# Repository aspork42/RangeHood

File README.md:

# RangeHood
# RangeHood
# RangeHood

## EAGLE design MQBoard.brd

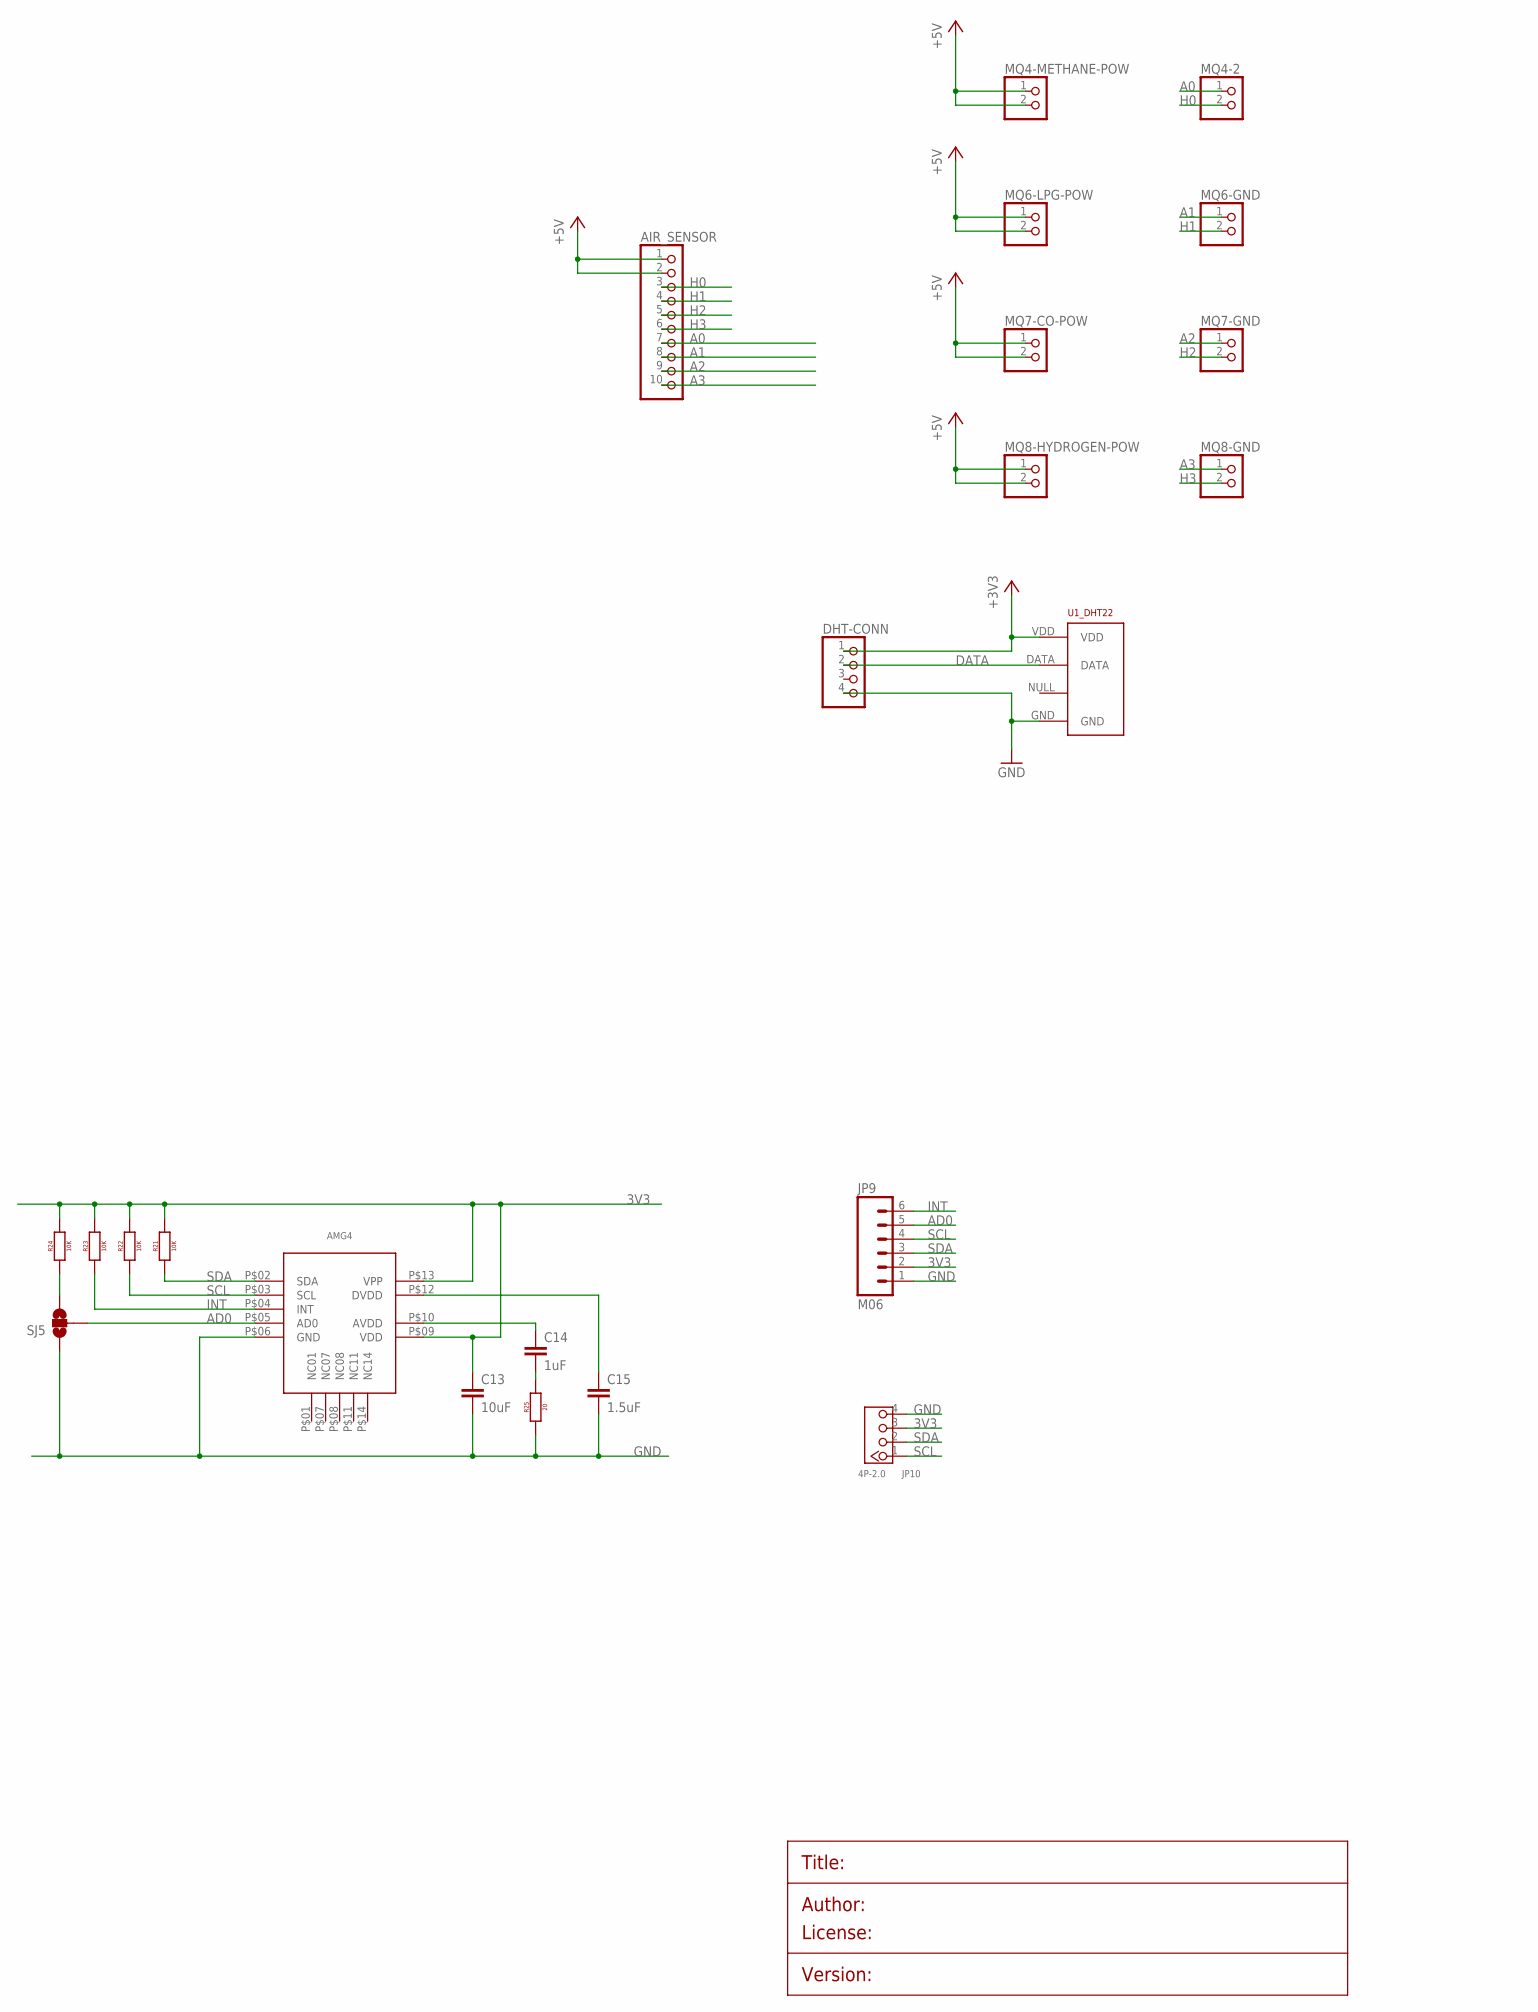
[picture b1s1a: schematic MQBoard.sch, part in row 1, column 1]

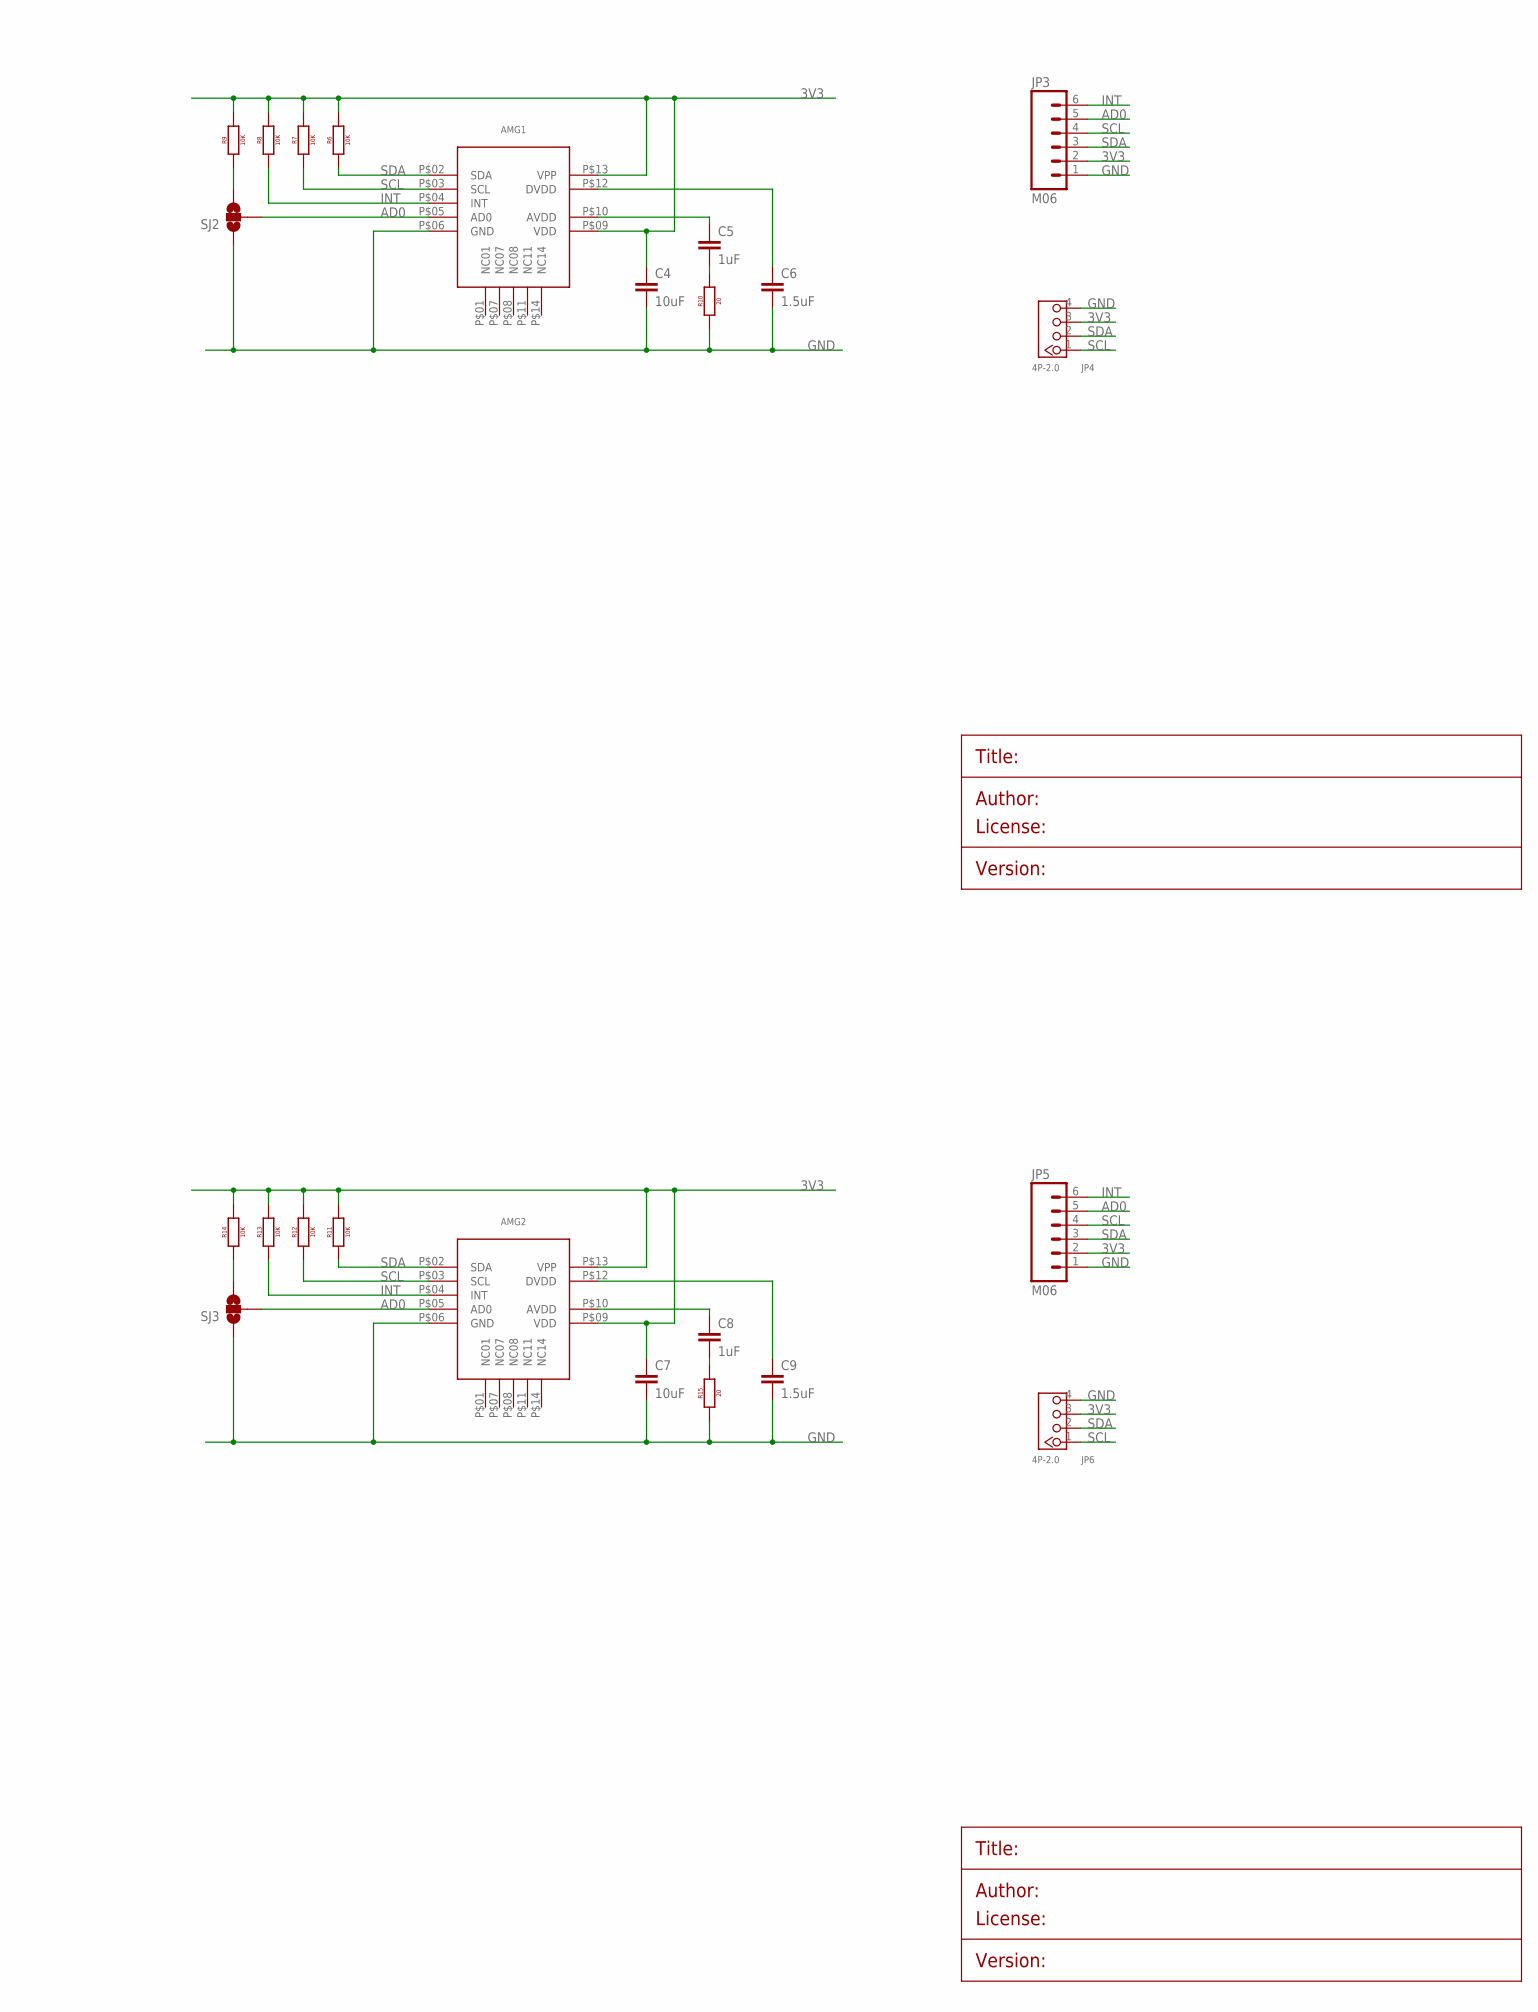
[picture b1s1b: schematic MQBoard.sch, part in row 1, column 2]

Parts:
AIR_SENSOR: PINHD-1X10; 1X10
AMG1, AMG2, AMG4: AMG88XX
C4, C7, C13: 10uF; 0805
C5, C8, C14: 1uF; 0805
C6, C9, C15: 1.5uF; 0805
DHT-CONN: PINHD-1X4; 1X04
JP3, JP5, JP9: M06; 1X06_NO_SILK
JP4, JP6, JP10: 4P-2.0; HW4-2.0
MQ4-2, MQ4-METHANE-POW, MQ6-GND, MQ6-LPG-POW, MQ7-CO-POW, MQ7-GND, MQ8-GND, MQ8-HYDROGEN-POW: PINHD-1X2; 1X02
R6, R7, R8, R9, R11, R12, R13, R14, R21, R22, R23, R24: 10K; 0805
R10, R15, R25: 20; 0805
SJ2, SJ3, SJ5: SOLDERJUMPER_2WAYS; SJ_3
U1_DHT22: RHT03_DHT-22_AM2302; RHT03_DHT-22

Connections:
3V3: AMG1.P$09 (VDD), AMG1.P$13 (VPP), AMG2.P$09 (VDD), AMG2.P$13 (VPP), AMG4.P$09 (VDD), AMG4.P$13 (VPP), C4.1, C7.1, C13.1, JP3.2, JP4.3, JP5.2, JP6.3, JP9.2, JP10.3, R6.2, R7.2, R8.2, R9.2, R11.2, R12.2, R13.2, R14.2, R21.2, R22.2, R23.2, R24.2
+3V3: DHT-CONN.1, U1_DHT22.VDD
+5V: AIR_SENSOR.1, AIR_SENSOR.2, MQ4-METHANE-POW.1, MQ4-METHANE-POW.2, MQ6-LPG-POW.1, MQ6-LPG-POW.2, MQ7-CO-POW.1, MQ7-CO-POW.2, MQ8-HYDROGEN-POW.1, MQ8-HYDROGEN-POW.2
A0: AIR_SENSOR.7, MQ4-2.1
A1: AIR_SENSOR.8, MQ6-GND.1
A2: AIR_SENSOR.9, MQ7-GND.1
A3: AIR_SENSOR.10, MQ8-GND.1
AD0: AMG1.P$05 (AD0), AMG2.P$05 (AD0), AMG4.P$05 (AD0), JP3.5, JP5.5, JP9.5, SJ2.2, SJ3.2, SJ5.2
DATA: DHT-CONN.2, U1_DHT22.DATA
GND: AMG1.P$06 (GND), AMG2.P$06 (GND), AMG4.P$06 (GND), C4.2, C6.2, C7.2, C9.2, C13.2, C15.2, DHT-CONN.4, JP3.1, JP4.4, JP5.1, JP6.4, JP9.1, JP10.4, R10.1, R15.1, R25.1, SJ2.1, SJ3.1, SJ5.1, U1_DHT22.GND
H0: AIR_SENSOR.3, MQ4-2.2
H1: AIR_SENSOR.4, MQ6-GND.2
H2: AIR_SENSOR.5, MQ7-GND.2
H3: AIR_SENSOR.6, MQ8-GND.2
INT: AMG1.P$04 (INT), AMG2.P$04 (INT), AMG4.P$04 (INT), JP3.6, JP5.6, JP9.6, R8.1, R13.1, R23.1
unnamed: AMG1.P$12 (DVDD), C6.1
unnamed: AMG1.P$10 (AVDD), C5.1
unnamed: R9.1, SJ2.3
unnamed: C5.2, R10.2
unnamed: AMG2.P$12 (DVDD), C9.1
unnamed: AMG2.P$10 (AVDD), C8.1
unnamed: R14.1, SJ3.3
unnamed: C8.2, R15.2
unnamed: AMG4.P$12 (DVDD), C15.1
unnamed: AMG4.P$10 (AVDD), C14.1
unnamed: R24.1, SJ5.3
unnamed: C14.2, R25.2
SCL: AMG1.P$03 (SCL), AMG2.P$03 (SCL), AMG4.P$03 (SCL), JP3.4, JP4.1, JP5.4, JP6.1, JP9.4, JP10.1, R7.1, R12.1, R22.1
SDA: AMG1.P$02 (SDA), AMG2.P$02 (SDA), AMG4.P$02 (SDA), JP3.3, JP4.2, JP5.3, JP6.2, JP9.3, JP10.2, R6.1, R11.1, R21.1

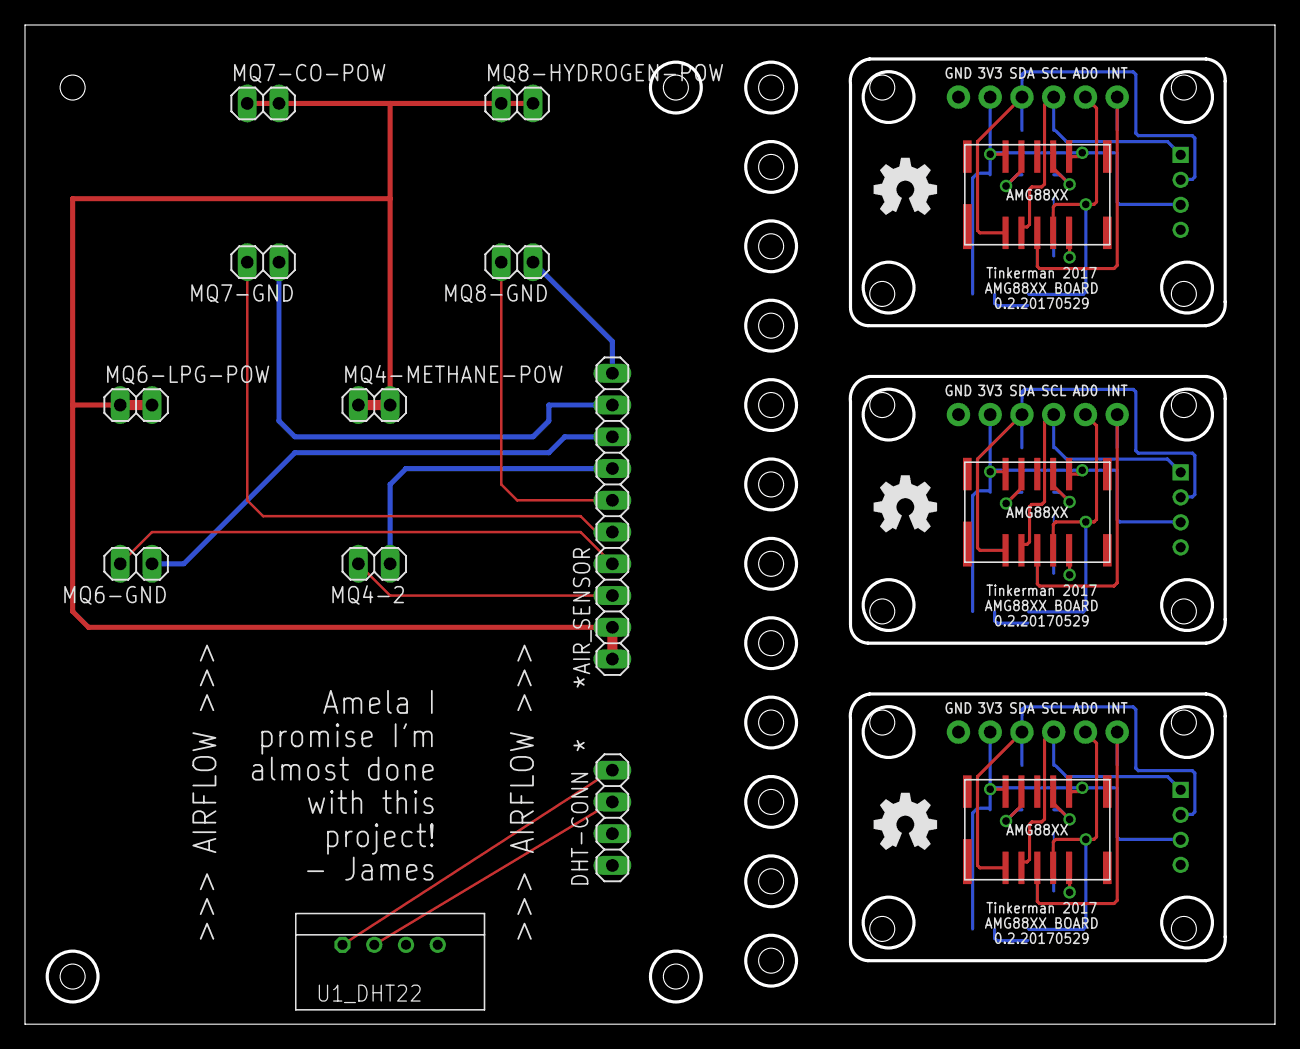
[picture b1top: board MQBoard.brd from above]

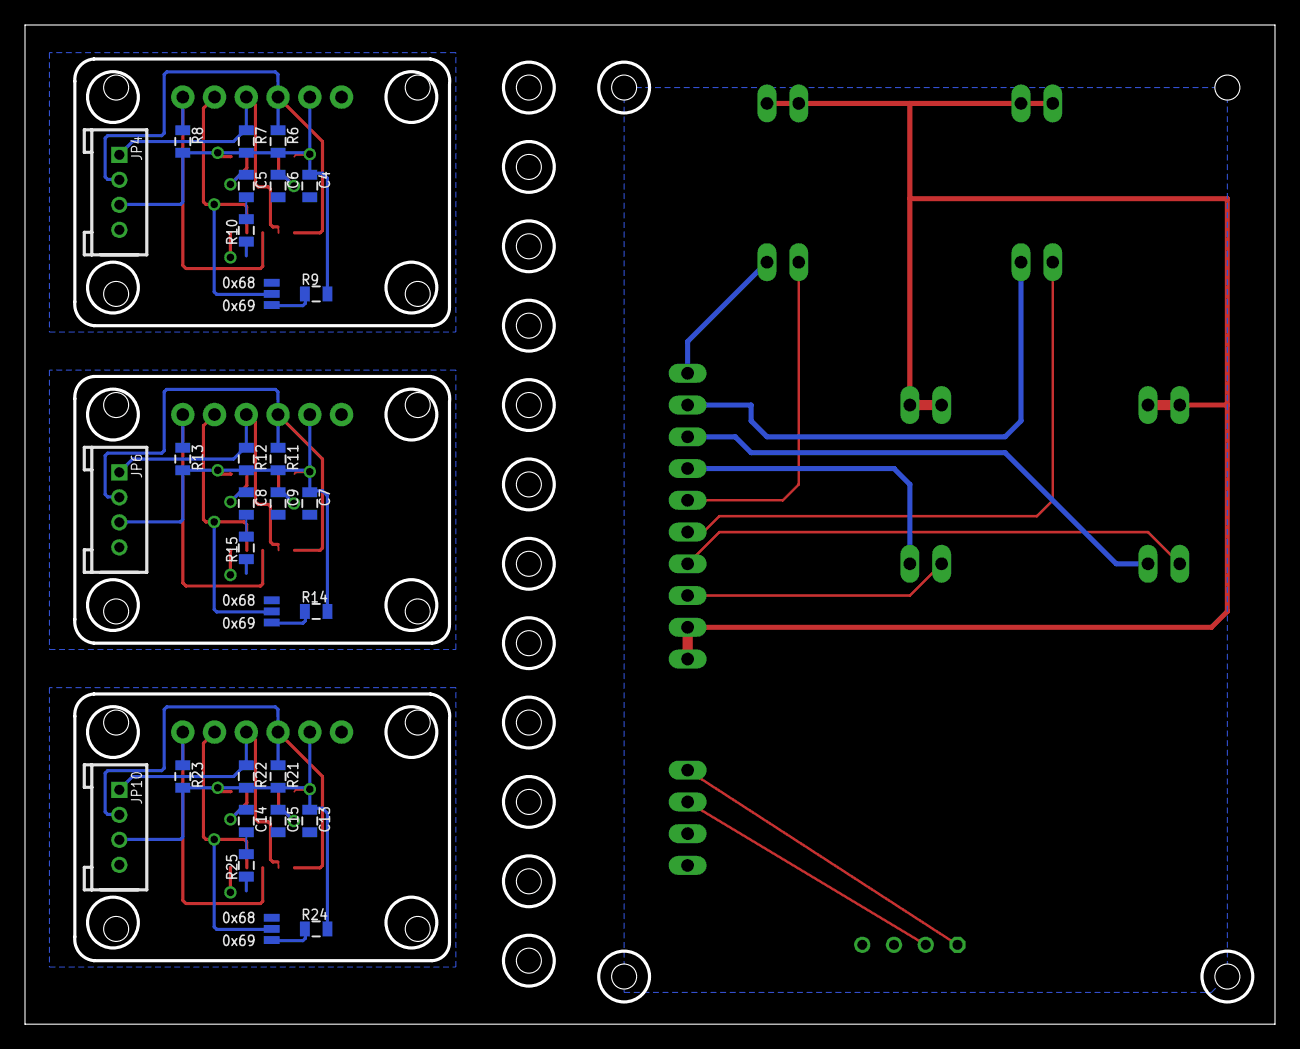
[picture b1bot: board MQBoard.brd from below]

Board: 2 copper layers, 99.7 x 79.7 mm, 47 parts (30 on the bottom side), 29 nets.

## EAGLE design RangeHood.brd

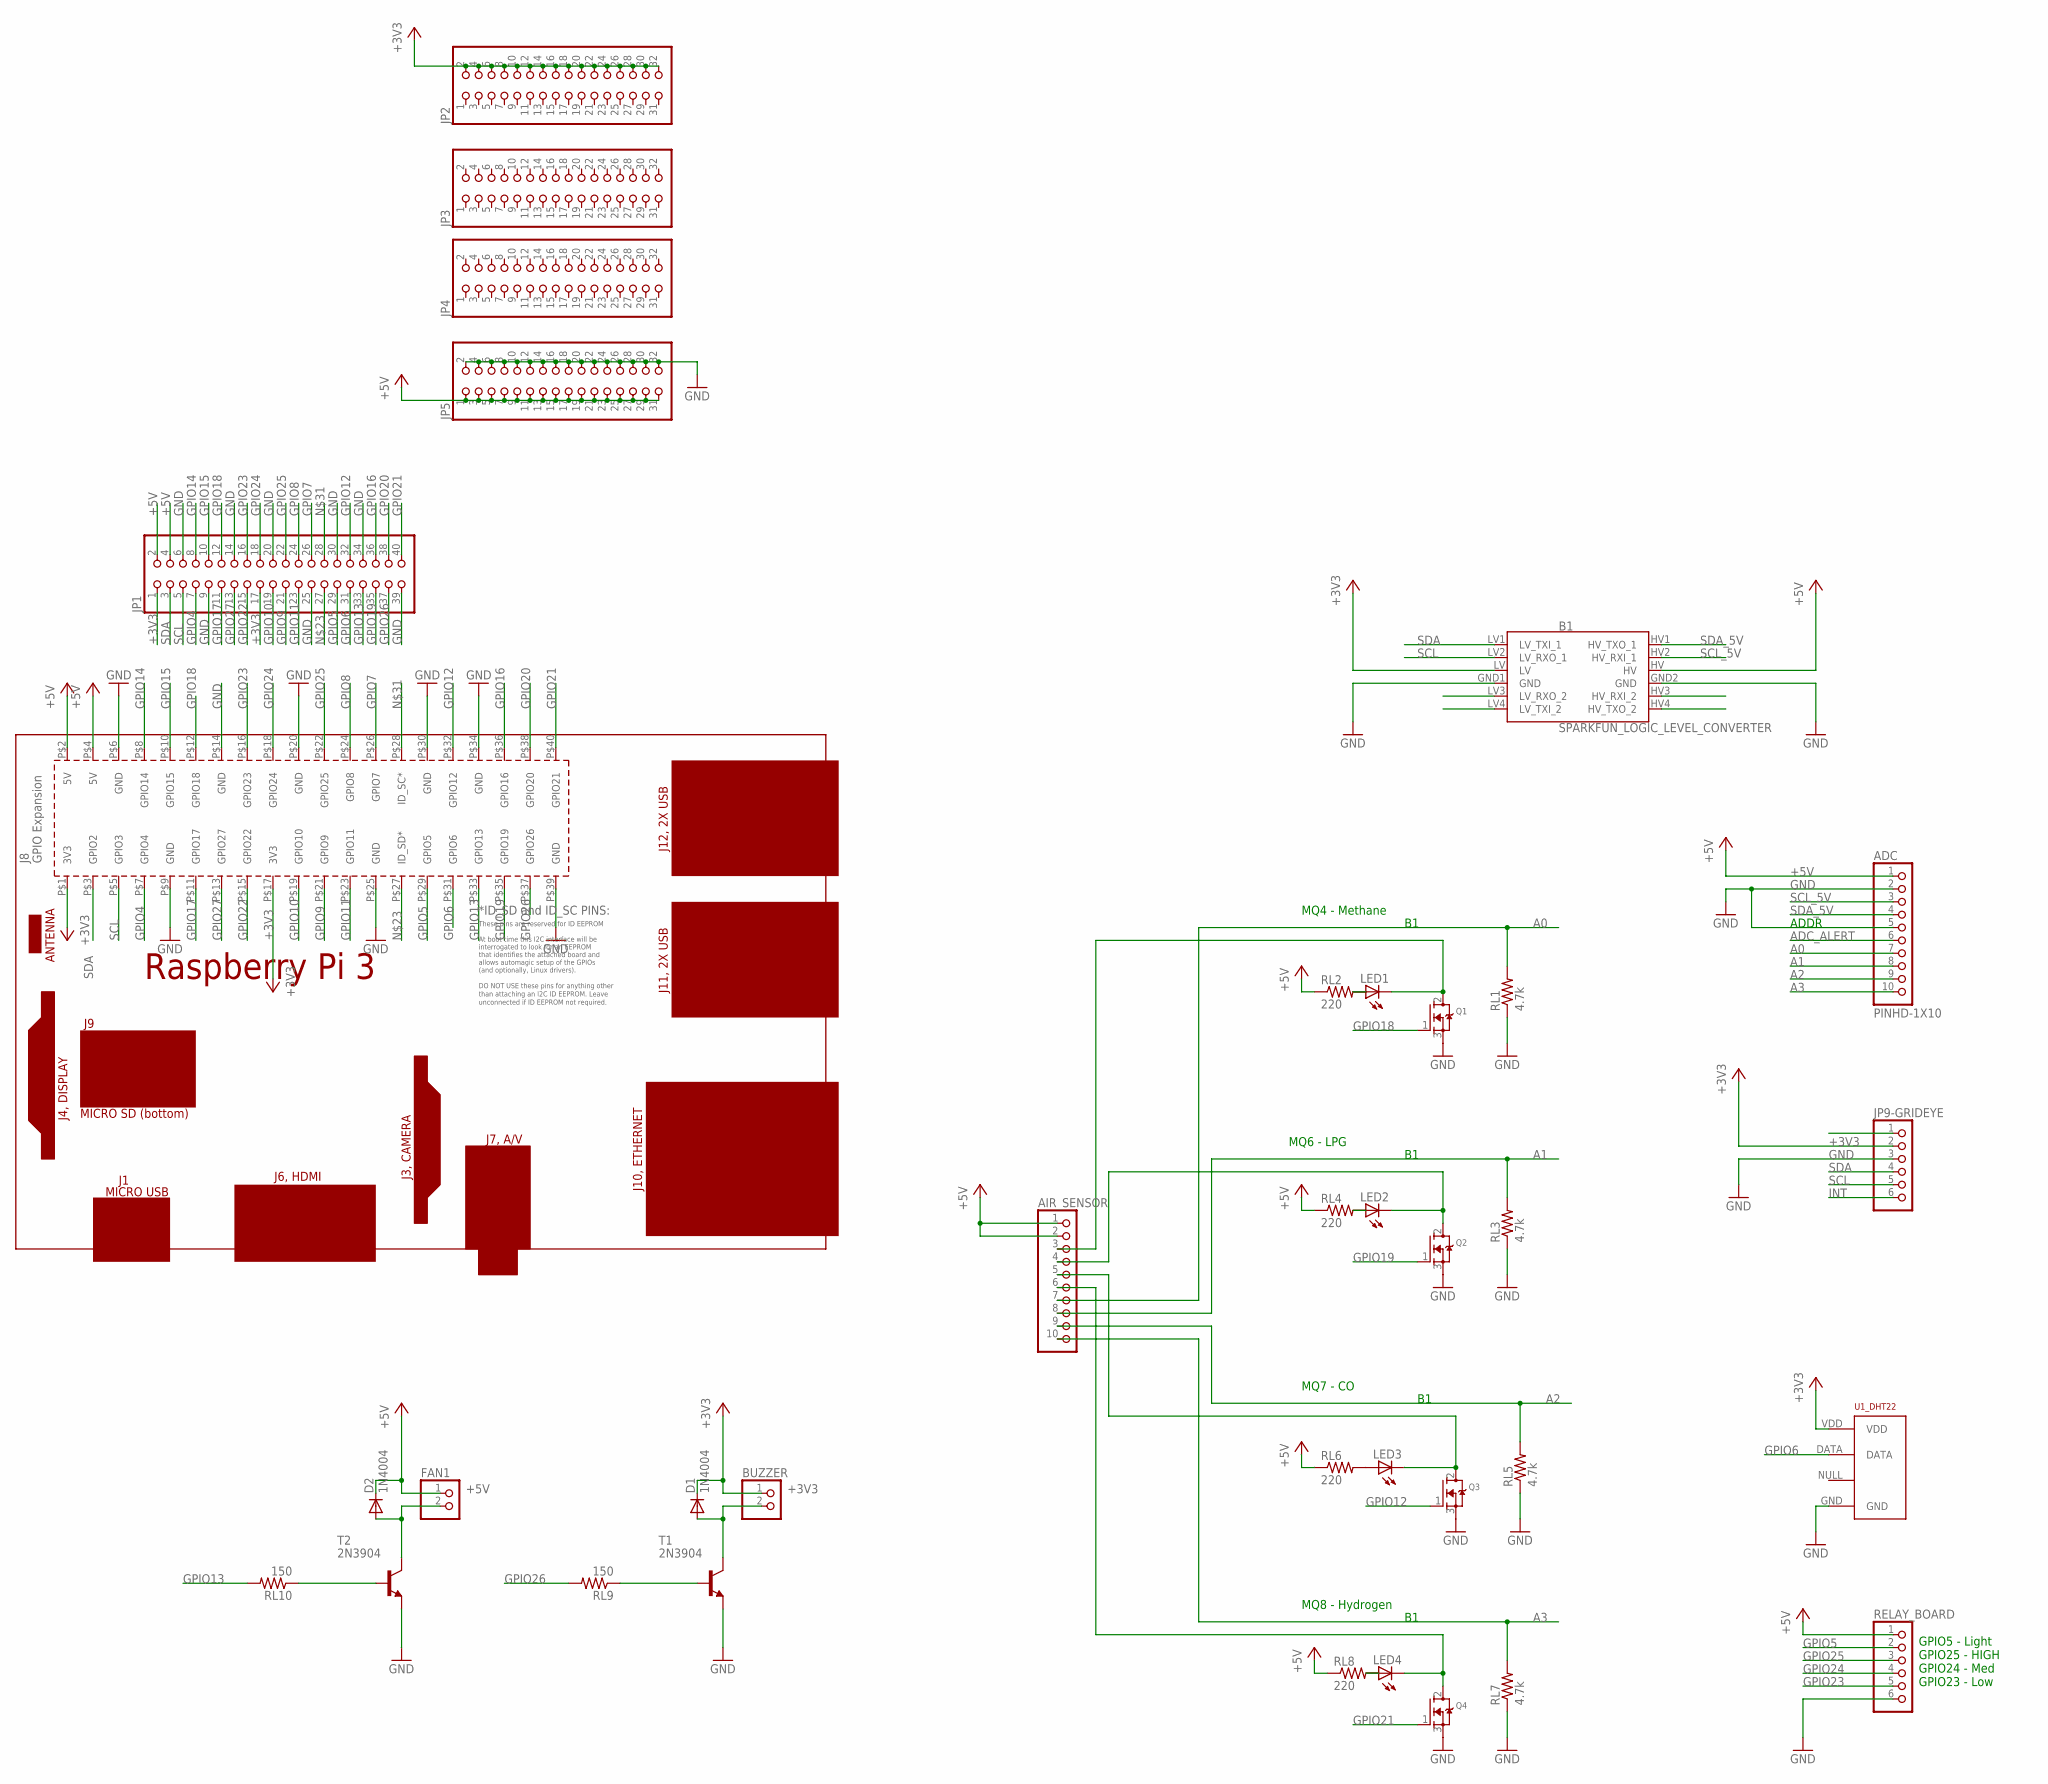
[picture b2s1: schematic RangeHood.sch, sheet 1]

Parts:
ADC: PINHD-1X10; 1X10-BIG
AIR_SENSOR: PINHD-1X10; 1X10
B1: SPARKFUN_LOGIC_LEVEL_CONVERTER
BUZZER: PINHD-1X2; 1X02
D1, D2: 1N4004; DO41-10
FAN1: PINHD-1X2; 1X02
JP1: PINHD-2X20; 2X20
JP2, JP3, JP4, JP5: PINHD-2X16; 2X16
JP9-GRIDEYE: PINHD-1X6; 1X06
LED1, LED2, LED3, LED4: LED3MM
PCB1: RPI3
Q1, Q2, Q3, Q4: MOSFET-NGDS_TO220V; TO220V
RELAY_BOARD: PINHD-1X6; 1X06
RL1, RL3, RL5, RL7: 4.7k; M0805
RL2, RL4, RL6, RL8: 220; M0805
RL9, RL10: 150; M0805
T1, T2: 2N3904; TO92
U1_DHT22: RHT03_DHT-22_AM2302; RHT03_DHT-22

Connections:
+3V3: B1.LV, BUZZER.1, D1.C, JP1.1, JP1.17, JP2.2, JP2.4, JP2.6, JP2.8, JP2.10, JP2.12, JP2.14, JP2.16, JP2.18, JP2.20, JP2.22, JP2.24, JP2.26, JP2.28, JP2.30, JP2.32, JP9-GRIDEYE.2, PCB1.P$1 (3V3), PCB1.P$17 (3V3), U1_DHT22.VDD
+5V: ADC.1, AIR_SENSOR.1, AIR_SENSOR.2, B1.HV, D2.C, FAN1.1, JP1.2, JP1.4, JP5.1, JP5.3, JP5.5, JP5.7, JP5.9, JP5.11, JP5.13, JP5.15, JP5.17, JP5.19, JP5.21, JP5.23, JP5.25, JP5.27, JP5.29, JP5.31, PCB1.P$2 (5V), PCB1.P$4 (5V), RELAY_BOARD.1, RL2.1, RL4.1, RL6.1, RL8.1
A0: ADC.7, AIR_SENSOR.7, RL1.2
A1: ADC.8, AIR_SENSOR.8, RL3.2
A2: ADC.9, AIR_SENSOR.9, RL5.2
A3: ADC.10, AIR_SENSOR.10, RL7.2
ADC_ALERT: ADC.6
GND: ADC.2, ADC.5, B1.GND1 (GND), B1.GND2 (GND), JP1.6, JP1.9, JP1.14, JP1.20, JP1.25, JP1.30, JP1.34, JP1.39, JP5.2, JP5.4, JP5.6, JP5.8, JP5.10, JP5.12, JP5.14, JP5.16, JP5.18, JP5.20, JP5.22, JP5.24, JP5.26, JP5.28, JP5.30, JP5.32, JP9-GRIDEYE.3, PCB1.P$6 (GND), PCB1.P$9 (GND), PCB1.P$14 (GND), PCB1.P$20 (GND), PCB1.P$25 (GND), PCB1.P$30 (GND), PCB1.P$34 (GND), PCB1.P$39 (GND), Q1.3 (S), Q2.3 (S), Q3.3 (S), Q4.3 (S), RELAY_BOARD.6, RL1.1, RL3.1, RL5.1, RL7.1, T1.3 (E), T2.3 (E), U1_DHT22.GND
GPIO4: JP1.7, PCB1.P$7 (GPIO4)
GPIO5: JP1.29, PCB1.P$29 (GPIO5), RELAY_BOARD.2
GPIO6: JP1.31, PCB1.P$31 (GPIO6), U1_DHT22.DATA
GPIO7: JP1.26, PCB1.P$26 (GPIO7)
GPIO8: JP1.24, PCB1.P$24 (GPIO8)
GPIO9: JP1.21, PCB1.P$21 (GPIO9)
GPIO10: JP1.19, PCB1.P$19 (GPIO10)
GPIO11: JP1.23, PCB1.P$23 (GPIO11)
GPIO12: JP1.32, PCB1.P$32 (GPIO12), Q3.1 (G)
GPIO13: JP1.33, PCB1.P$33 (GPIO13), RL10.2
GPIO14: JP1.8, PCB1.P$8 (GPIO14)
GPIO15: JP1.10, PCB1.P$10 (GPIO15)
GPIO16: JP1.36, PCB1.P$36 (GPIO16)
GPIO17: JP1.11, PCB1.P$11 (GPIO17)
GPIO18: JP1.12, PCB1.P$12 (GPIO18), Q1.1 (G)
GPIO19: JP1.35, PCB1.P$35 (GPIO19), Q2.1 (G)
GPIO20: JP1.38, PCB1.P$38 (GPIO20)
GPIO21: JP1.40, PCB1.P$40 (GPIO21), Q4.1 (G)
GPIO22: JP1.15, PCB1.P$15 (GPIO22)
GPIO23: JP1.16, PCB1.P$16 (GPIO23), RELAY_BOARD.5
GPIO24: JP1.18, PCB1.P$18 (GPIO24), RELAY_BOARD.4
GPIO25: JP1.22, PCB1.P$22 (GPIO25), RELAY_BOARD.3
GPIO26: JP1.37, PCB1.P$37 (GPIO26), RL9.2
GPIO27: JP1.13, PCB1.P$13 (GPIO27)
INT: JP9-GRIDEYE.6
unnamed: LED2.A, RL4.2
unnamed: AIR_SENSOR.5, LED3.K (C), Q3.2 (D)
unnamed: LED1.A, RL2.2
unnamed: AIR_SENSOR.3, LED1.K (C), Q1.2 (D)
unnamed: LED3.A, RL6.2
unnamed: D2.A, FAN1.2, T2.1 (C)
unnamed: LED4.A, RL8.2
unnamed: AIR_SENSOR.6, LED4.K (C), Q4.2 (D)
unnamed: BUZZER.2, D1.A, T1.1 (C)
unnamed: RL9.1, T1.2 (B)
unnamed: RL10.1, T2.2 (B)
unnamed: JP1.27, PCB1.P$27 (ID_SD*)
unnamed: JP1.28, PCB1.P$28 (ID_SC*)
unnamed: AIR_SENSOR.4, LED2.K (C), Q2.2 (D)
SCL: B1.LV2 (LV_RXO_1), JP1.5, JP9-GRIDEYE.5, PCB1.P$5 (GPIO3)
SCL_5V: ADC.3, B1.HV2 (HV_RXI_1)
SDA: B1.LV1 (LV_TXI_1), JP1.3, JP9-GRIDEYE.4, PCB1.P$3 (GPIO2)
SDA_5V: ADC.4, B1.HV1 (HV_TXO_1)

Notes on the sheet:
ADDR
GPIO5 - Light GPIO25 - HIGH GPIO24 - Med GPIO23 - Low
MQ4 - Methane
MQ6 - LPG
MQ7 - CO
MQ8 - Hydrogen

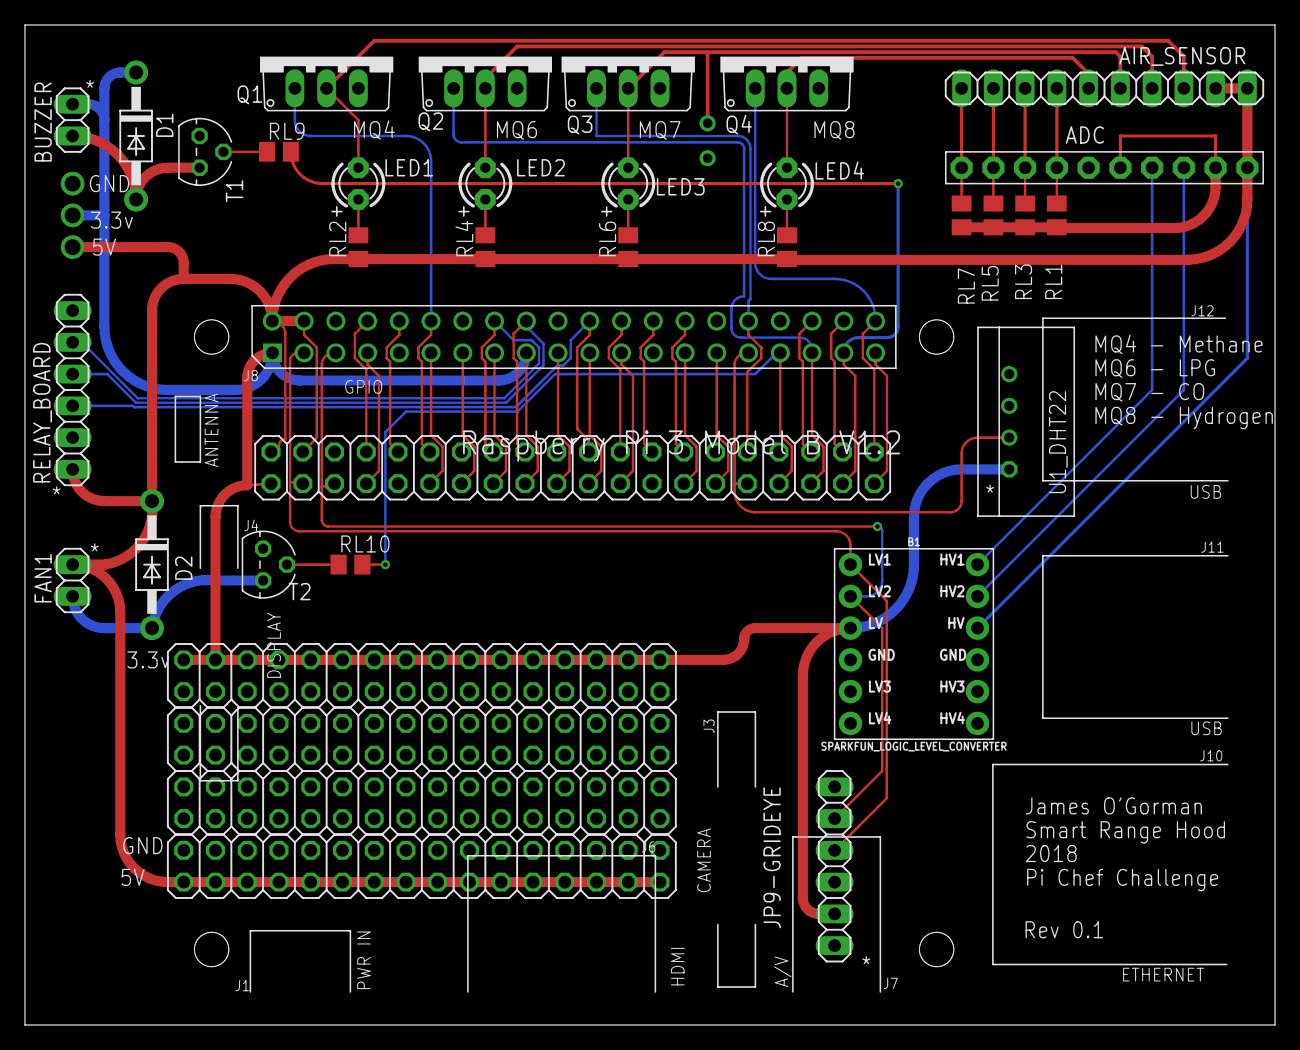
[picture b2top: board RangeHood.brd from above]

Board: 2 copper layers, 100.0 x 80.0 mm, 36 parts (0 on the bottom side), 49 nets.

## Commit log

2018-03-07 Add files via upload
    Rev 0.00 - Unfinished partial design.
2018-03-09 Add files via upload
    Updates from 3/7/2018.
    Added ground plane; all traces routed.

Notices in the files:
parts and their libraries:
SparkFun-Boards: Licensing: Creative Commons ShareAlike 4.0 International - https://creativecommons.org/licenses/by-sa/4.0
